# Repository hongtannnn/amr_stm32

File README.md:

# AMR Hardware & PCB Design (amr_stm32)

A low-level controller board and hardware system designed as the foundation for an Autonomous Mobile Robot (AMR). The project focuses on real-time task processing, sensor communication, and motor control in preparation for future integration with ROS 2, SLAM algorithms, and autonomous navigation.

## 📸 Board Preview

| 3D Render | Bare PCB (Unassembled) | Real Board (Assembled) |
| :---: | :---: | :---: |
|  |  |  |
| *Completed PCB design featuring peripheral connectors, power supply block, and central microcontroller.* | *Newly fabricated AMR v1.0 bare board, showing silkscreen details and routing before component assembly.* | *Actual assembled PCB (AMR v1.0) with all components soldered and ready for testing.* |

## 🚀 Hardware Features

-   **Central Microcontroller (MCU):** Utilizes the **STM32F405RGT6** chip, providing powerful processing capabilities for PID algorithms and high-speed encoder reading.
-   **Industrial-grade Design:** 4-layer layout with dedicated GND and Power (VCC) planes, ensuring Signal Integrity and Electromagnetic Interference (EMI) reduction when operating in environments with electrical motors.

## 🛠 Tools & Software

-   **Hardware Design (EDA):** KiCad
-   **Embedded Programming:** STM32CubeIDE / STM32CubeMX
-   **Mechanical Design (CAD):** Autodesk Fusion 360

## 🎯 Future Roadmap

- [ ] Complete basic Firmware: Read encoders, control DC/BLDC motors via PID.
- [ ] Establish stable UART/I2C communication protocols between the STM32 and embedded computers (Raspberry Pi/Mini PC).
- [ ] Integrate the microcontroller package into the **ROS 2** network (using micro-ROS or rosserial).
- [ ] Deploy LiDAR and IMU sensors for mapping (SLAM) and navigation.

---
**Author:** Truong Hong Tan (@hongtannnn)  
*Student at the University of Engineering and Technology (UET) - Vietnam National University, Hanoi.*

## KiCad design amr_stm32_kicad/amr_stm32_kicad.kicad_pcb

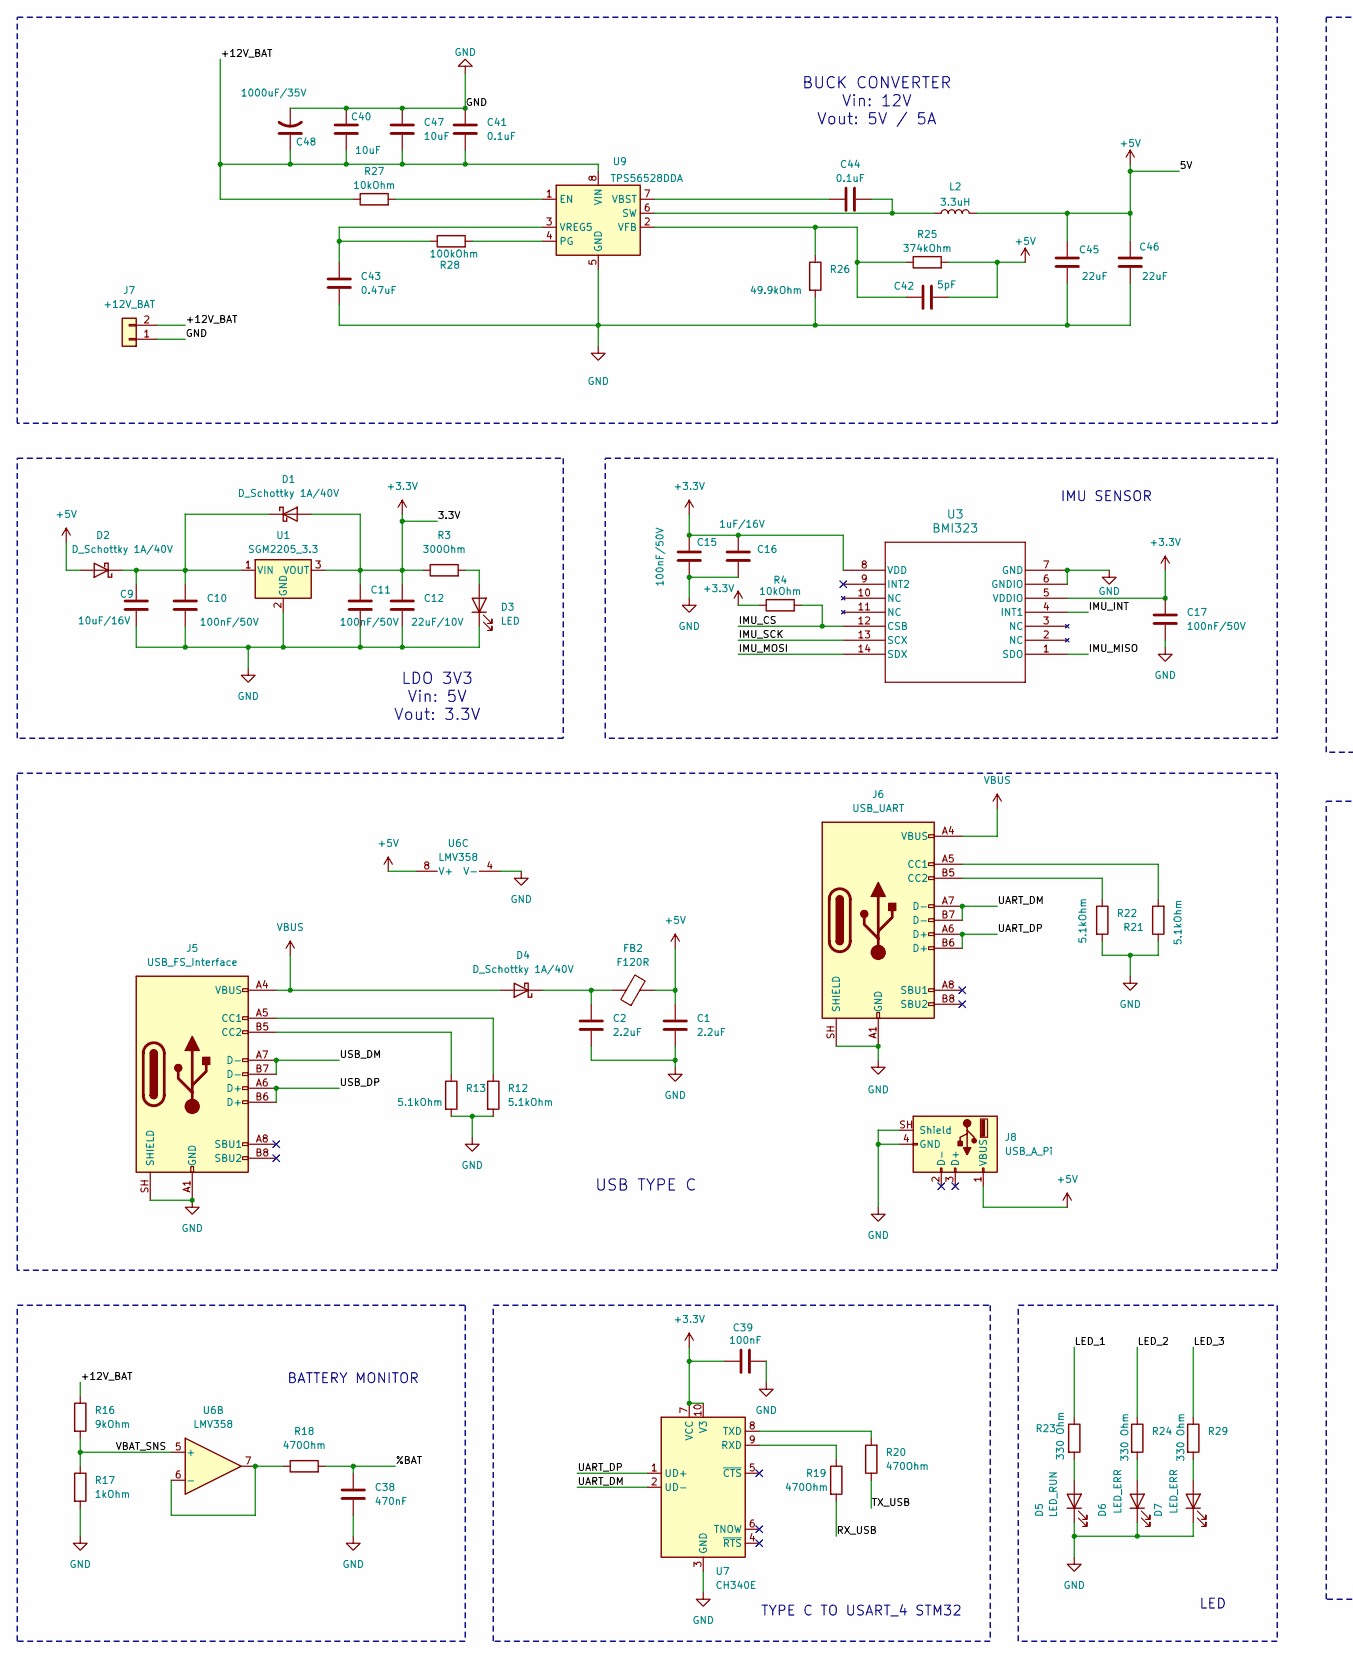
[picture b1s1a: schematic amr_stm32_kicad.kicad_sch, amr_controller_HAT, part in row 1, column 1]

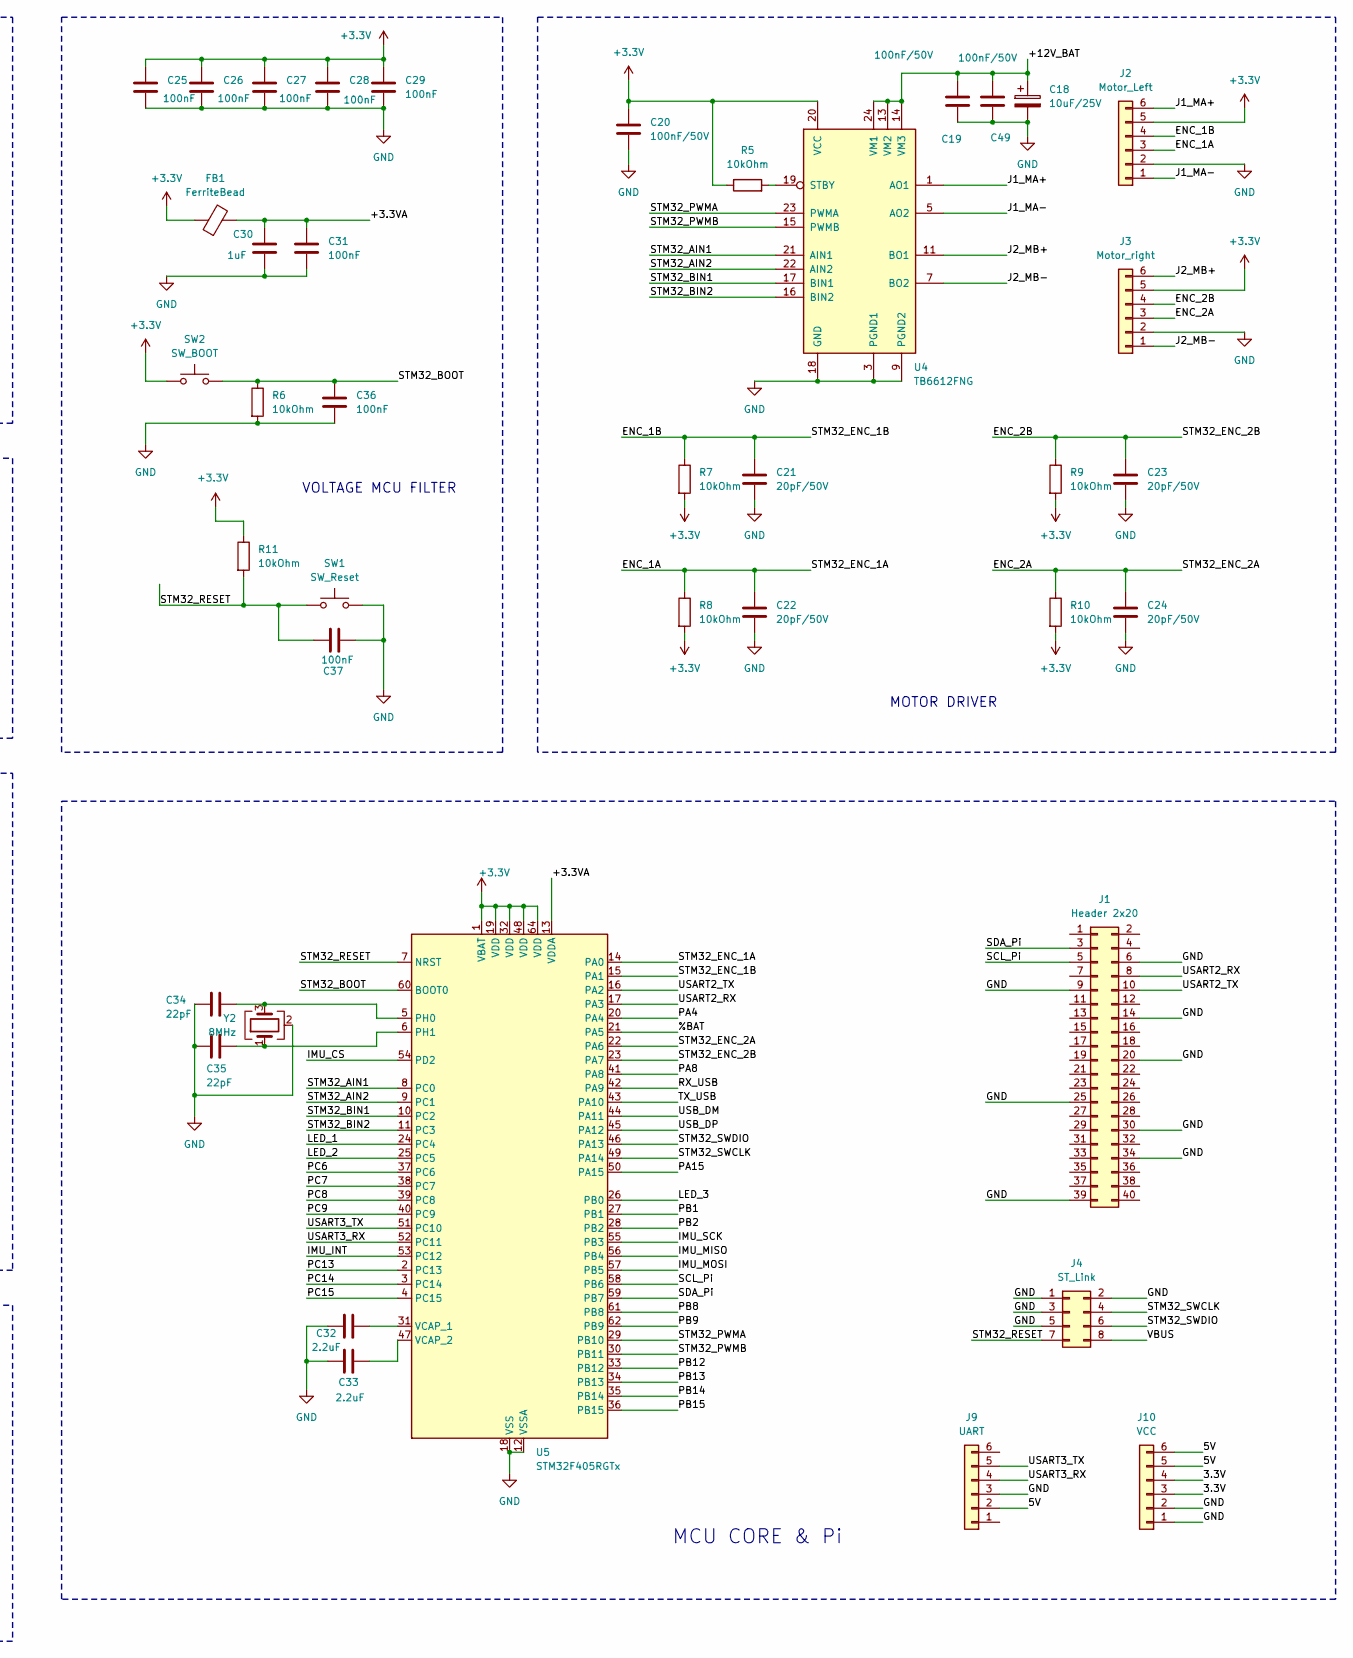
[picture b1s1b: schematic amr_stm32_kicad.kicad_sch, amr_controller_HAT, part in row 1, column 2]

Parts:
C1, C2: 2.2uF; C_0603_1608Metric
C9: 10uF/16V; C_0805_2012Metric
C10, C11, C15, C17, C19, C20, C49: 100nF/50V; C_0805_2012Metric
C12: 22uF/10V; C_0805_2012Metric
C16: 1uF/16V; C_0805_2012Metric
C18: 10uF/25V; CP_Elec_6.3x7.7
C21, C22, C23, C24: 20pF/50V; C_0805_2012Metric
C25, C26, C27, C28, C29, C31, C36, C37, C39: 100nF; C_0603_1608Metric
C30: 1uF; C_0603_1608Metric
C32, C33: 2.2uF; C_0805_2012Metric
C34, C35: 22pF; C_0603_1608Metric
C38: 470nF; C_0603_1608Metric
C40, C47: 10uF; C_1206_3216Metric
C41, C44: 0.1uF; C_0603_1608Metric
C42: 5pF; C_0603_1608Metric
C43: 0.47uF; C_0603_1608Metric
C45, C46: 22uF; C_1206_3216Metric
C48: 1000uF/35V; CP_Radial_D10.0mm_P5.00mm
D1, D2, D4: D_Schottky 1A/40V; D_SOD-123
D3: LED; LED_0805_2012Metric
D5: LED_RUN; LED_0603_1608Metric
D6, D7: LED_ERR; LED_0603_1608Metric
FB1: FerriteBead; L_0805_2012Metric
FB2: F120R; L_0603_1608Metric
J1: Header 2x20; PinHeader_2x20_P2.54mm_Vertical
J2: Motor_Left; JST_PH_S6B-PH-K_1x06_P2.00mm_Horizontal
J3: Motor_right; JST_PH_S6B-PH-K_1x06_P2.00mm_Horizontal
J4: ST_Link; PinHeader_2x04_P2.54mm_Horizontal
J5: USB_FS_Interface; USB_C_Receptacle_HRO_TYPE-C-31-M-12
J6: USB_UART; USB_C_Receptacle_HRO_TYPE-C-31-M-12
J7: +12V_BAT; AMASS_XT60PW-M_1x02_P7.20mm_Horizontal
J8: USB_A_Pi; USB_A_Molex_67643_Horizontal
J9: UART; PinSocket_1x06_P2.54mm_Vertical
J10: VCC; PinSocket_1x06_P2.54mm_Vertical
L2: 3.3uH; L_7.3x7.3_H4.5
R3: 300Ohm; R_0805_2012Metric
R4, R5, R7, R8, R9, R10: 10kOhm; R_0805_2012Metric
R6, R11, R27: 10kOhm; R_0603_1608Metric
R12, R13, R21, R22: 5.1kOhm; R_0603_1608Metric
R16: 9kOhm; R_0603_1608Metric
R17: 1kOhm; R_0603_1608Metric
R18, R19, R20: 470Ohm; R_0603_1608Metric
R23, R24, R29: 330 Ohm; R_0603_1608Metric
R25: 374kOhm; R_0603_1608Metric
R26: 49.9kOhm; R_0603_1608Metric
R28: 100kOhm; R_0603_1608Metric
SW1: SW_Reset; SW_SPST_B3U-1000P
SW2: SW_BOOT; SW_SPST_B3U-1000P
U1: SGM2205_3.3; SOT-223-3_TabPin2
U3: BMI323; BMI323_BOS-L
U4: TB6612FNG; SSOP-24_5.3x8.2mm_P0.65mm
U5: STM32F405RGTx; LQFP-64_10x10mm_P0.5mm
U6: LMV358; SOIC-8_3.9x4.9mm_P1.27mm
U7: CH340E; MSOP-10_3x3mm_P0.5mm
U9: TPS56528DDA; Texas_HSOP-8-1EP_3.9x4.9mm_P1.27mm_ThermalVias
Y2: 8MHz; Crystal_SMD_5032-4Pin_5.0x3.2mm

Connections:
+3.3V: C11.1, C12.1, C15.1, C16.1, C17.1, C20.1, C25.1, C26.1, C27.1, C28.1, C29.1, C39.1, D1.2 (A), FB1.1, J2.5, J3.5, J10.3, J10.4, R3.1, R4.1, R5.1, R7.2, R8.2, R9.2, R10.2, R11.1, SW2.1, U1.3 (VOUT), U3.5 (VDDIO), U3.8 (VDD), U4.20 (VCC), U5.1 (VBAT), U5.19 (VDD), U5.32 (VDD), U5.48 (VDD), U5.64 (VDD), U7.7 (VCC), U7.10 (V3)
+5V: C1.1, C42.1, C45.1, C46.1, D2.2 (A), FB2.2, J8.1 (VBUS), J9.2, J10.5, J10.6, L2.1, R25.2, U6.8 (V+)
/%BAT: C38.1, R18.2, U5.21 (PA5)
/+3.3VA: C30.1, C31.1, FB1.2, U5.13 (VDDA)
/+12V_BAT: C18.1, C19.1, C40.2, C41.2, C47.2, C48.1, C49.1, J7.2, R16.1, R27.1, U4.13 (VM2), U4.14 (VM3), U4.24 (VM1), U9.8 (VIN)
/ENC_1A: C22.1, J2.3, R8.1, U5.14 (PA0)
/ENC_1B: C21.1, J2.4, R7.1, U5.15 (PA1)
/ENC_2A: C24.1, J3.3, R10.1, U5.22 (PA6)
/ENC_2B: C23.1, J3.4, R9.1, U5.23 (PA7)
/IMU_CS: R4.2, U3.12 (CSB), U5.54 (PD2)
/IMU_INT: U3.4 (INT1), U5.53 (PC12)
/IMU_MISO: U3.1 (SDO), U5.56 (PB4)
/IMU_MOSI: U3.14 (SDX), U5.57 (PB5)
/IMU_SCK: U3.13 (SCX), U5.55 (PB3)
/J1_MA+: J2.6, U4.1 (AO1), U4.2 (AO1)
/J1_MA-: J2.1, U4.5 (AO2), U4.6 (AO2)
/J2_MB+: J3.6, U4.11 (BO1), U4.12 (BO1)
/J2_MB-: J3.1, U4.7 (BO2), U4.8 (BO2)
/LED_1: R23.1, U5.24 (PC4)
/LED_2: R24.1, U5.25 (PC5)
/LED_3: R29.1, U5.26 (PB0)
/PA4: U5.20 (PA4)
/PA8: U5.41 (PA8)
/PA15: U5.50 (PA15)
/PB1: U5.27 (PB1)
/PB2: U5.28 (PB2)
/PB8: U5.61 (PB8)
/PB9: U5.62 (PB9)
/PB12: U5.33 (PB12)
/PB13: U5.34 (PB13)
/PB14: U5.35 (PB14)
/PB15: U5.36 (PB15)
/PC6: U5.37 (PC6)
/PC7: U5.38 (PC7)
/PC8: U5.39 (PC8)
/PC9: U5.40 (PC9)
/PC13: U5.2 (PC13)
/PC14: U5.3 (PC14)
/PC15: U5.4 (PC15)
/RX_USB: R19.2, U5.42 (PA9)
/SCL_Pi: J1.5, U5.58 (PB6)
/SDA_Pi: J1.3, U5.59 (PB7)
/STM32_AIN1: U4.21 (AIN1), U5.8 (PC0)
/STM32_AIN2: U4.22 (AIN2), U5.9 (PC1)
/STM32_BIN1: U4.17 (BIN1), U5.10 (PC2)
/STM32_BIN2: U4.16 (BIN2), U5.11 (PC3)
/STM32_BOOT: C36.1, R6.1, SW2.2, U5.60 (BOOT0)
/STM32_PWMA: U4.23 (PWMA), U5.29 (PB10)
/STM32_PWMB: U4.15 (PWMB), U5.30 (PB11)
/STM32_RESET: C37.1, J4.7, R11.2, SW1.1, U5.7 (NRST)
/STM32_SWCLK: J4.4, U5.49 (PA14)
/STM32_SWDIO: J4.6, U5.46 (PA13)
/TX_USB: R20.1, U5.43 (PA10)
/UART_DM: J6.A7 (D-), J6.B7 (D-), U7.2 (UD-)
/UART_DP: J6.A6 (D+), J6.B6 (D+), U7.1 (UD+)
/USART2_RX: J1.8, U5.17 (PA3)
/USART2_TX: J1.10, U5.16 (PA2)
/USART3_RX: J9.4, U5.52 (PC11)
/USART3_TX: J9.5, U5.51 (PC10)
/USB_DM: J5.A7 (D-), J5.B7 (D-), U5.44 (PA11)
/USB_DP: J5.A6 (D+), J5.B6 (D+), U5.45 (PA12)
/VBAT_SNS: R16.2, R17.1, U6.5 (+)
GND: C1.2, C2.2, C9.2, C10.2, C11.2, C12.2, C15.2, C16.2, C17.2, C18.2, C19.2, C20.2, C21.2, C22.2, C23.2, C24.2, C25.2, C26.2, C27.2, C28.2, C29.2, C30.2, C31.2, C32.1, C33.1, C34.2, C35.2, C36.2, C37.2, C38.2, C39.2, C40.1, C41.1, C43.2, C45.2, C46.2, C47.1, C48.2, C49.2, D3.1 (K), D5.1 (K), D6.1 (K), D7.1 (K), J1.6, J1.9, J1.14, J1.20, J1.25, J1.30, J1.34, J1.39, J2.2, J3.2, J4.1, J4.2, J4.3, J4.5, J5.A1 (GND), J5.A12 (GND), J5.B1 (GND), J5.B12 (GND), J5.SH (SHIELD), J6.A1 (GND), J6.A12 (GND), J6.B1 (GND), J6.B12 (GND), J6.SH (SHIELD), J7.1, J8.4 (GND), J8.SH (Shield), J9.3, J10.1, J10.2, R6.2, R12.2, R13.2, R17.2, R21.1, R22.2, R26.2, SW1.2, U1.2 (GND), U3.6 (GNDIO), U3.7 (GND), U4.3 (PGND1), U4.4 (PGND1), U4.9 (PGND2), U4.10 (PGND2), U4.18 (GND), U5.12 (VSSA), U5.18 (VSS), U5.63 (VSS), U6.4 (V-), U7.3 (GND), U9.5 (GND), U9.9 (GND), Y2.2 (G), Y2.4 (G)
unnamed: C9.1, C10.1, D1.1 (K), D2.1 (K), U1.1 (VIN)
unnamed: D3.2 (A), R3.2
unnamed: C2.1, D4.1 (K), FB2.1
unnamed: D5.2 (A), R23.2
unnamed: D6.2 (A), R24.2
unnamed: D7.2 (A), R29.2
unnamed: J5.A5 (CC1), R12.1
unnamed: J5.B5 (CC2), R13.1
unnamed: J6.A5 (CC1), R21.2
unnamed: J6.B5 (CC2), R22.1
unnamed: R5.2, U4.19 (STBY)
unnamed: C34.1, U5.5 (PH0), Y2.3
unnamed: C35.1, U5.6 (PH1), Y2.1
unnamed: C32.2, U5.31 (VCAP_1)
unnamed: C33.2, U5.47 (VCAP_2)
unnamed: R18.1, U6.6 (-), U6.7
unnamed: R19.1, U7.9 (RXD)
unnamed: R20.2, U7.8 (TXD)
unnamed: R27.2, U9.1 (EN)
unnamed: R28.2, U9.4 (PG)
unnamed: C44.2, L2.2, U9.6 (SW)
unnamed: C44.1, U9.7 (VBST)
unnamed: C42.2, R25.1, R26.1, U9.2 (VFB)
unnamed: C43.1, R28.1, U9.3 (VREG5)
VBUS: D4.2 (A), J4.8, J5.A4 (VBUS), J5.A9 (VBUS), J5.B4 (VBUS), J5.B9 (VBUS), J6.A4 (VBUS), J6.A9 (VBUS), J6.B4 (VBUS), J6.B9 (VBUS)

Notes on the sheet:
BUCK CONVERTER Vin: 12V Vout: 5V / 5A
IMU SENSOR
MCU CORE & Pi
TYPE C TO USART_4 STM32
BATTERY MONITOR
USB TYPE C
LED
VOLTAGE MCU FILTER
MOTOR DRIVER
LDO 3V3 Vin: 5V Vout: 3.3V

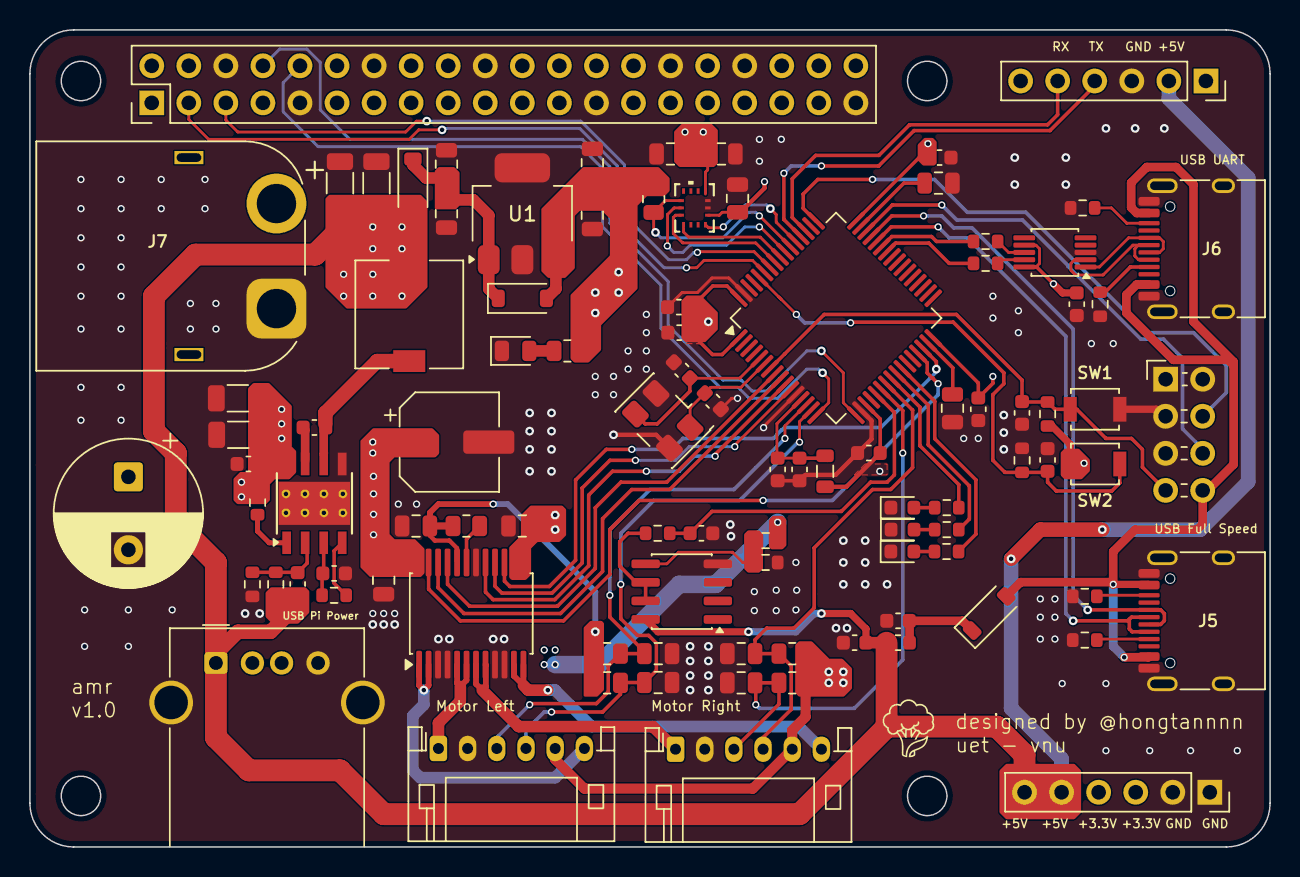
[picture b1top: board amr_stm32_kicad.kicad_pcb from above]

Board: 4 copper layers, 85.0 x 56.0 mm, 96 parts (0 on the bottom side), 70 nets.

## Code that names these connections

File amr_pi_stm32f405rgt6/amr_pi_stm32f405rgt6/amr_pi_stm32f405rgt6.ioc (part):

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Mcu.Name=STM32F405RGTx
Mcu.Package=LQFP64
Mcu.UserName=STM32F405RGTx
PA0-WKUP.Signal=S_TIM5_CH1
PA1.Signal=S_TIM5_CH2
PA10.Mode=Asynchronous
PA10.Signal=USART1_RX
PA11.Signal=USB_OTG_FS_DM
PA12.Signal=USB_OTG_FS_DP
PA13.Signal=SYS_JTMS-SWDIO
PA14.Signal=SYS_JTCK-SWCLK
PA2.Signal=USART2_TX
PA3.Signal=USART2_RX
PA5.Signal=ADCx_IN5
PA6.Signal=S_TIM3_CH1
PA7.Signal=S_TIM3_CH2
PA9.Mode=Asynchronous
PA9.Signal=USART1_TX
PB0.Signal=GPIO_Output
PB10.Signal=S_TIM2_CH3
PB11.Signal=S_TIM2_CH4
PB3.Mode=Full_Duplex_Master
PB3.Signal=SPI1_SCK
PB4.Mode=Full_Duplex_Master
PB4.Signal=SPI1_MISO
PB5.Mode=Full_Duplex_Master
PB5.Signal=SPI1_MOSI
PB6.Signal=I2C1_SCL
PB7.Signal=I2C1_SDA
PC0.Signal=GPIO_Output
PC1.Signal=GPIO_Output
PC10.Signal=USART3_TX
PC11.Signal=USART3_RX
PC12.Signal=GPXTI12
PC2.Signal=GPIO_Output
PC3.Signal=GPIO_Output
PC4.Signal=GPIO_Output
PC5.Signal=GPIO_Output
PD2.GPIOParameters=GPIO_Speed
PD2.GPIO_Speed=GPIO_SPEED_FREQ_VERY_HIGH
PD2.Signal=GPIO_Output
PH0-OSC_IN.Mode=HSE-External-Oscillator
PH0-OSC_IN.Signal=RCC_OSC_IN
PH1-OSC_OUT.Mode=HSE-External-Oscillator
PH1-OSC_OUT.Signal=RCC_OSC_OUT
RCC.HSE_VALUE=24000000
RCC.SYSCLKFreq_VALUE=168000000
RCC.SYSCLKSource=RCC_SYSCLKSOURCE_PLLCLK
board=custom
